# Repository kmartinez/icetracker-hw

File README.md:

# GDP Glacier Monitor

## Name
GDP Glacier Monitor - Hardware - part of the glacsweb.org project at The University of Southampton

## File Info
```
├── GlacTracker_PSU_V1
│   ├── GlacTracker_PSU.brd - EAGLE board file
│   ├── GlacTracker_PSU.sch - EAGLE schematic file
│   ├── GlacTracker_PSU_BOM.xlsx - Overall BOM
│   ├── mgc1g18_GlacTracker_PSU.zip - Gerber Files
│   ├── mgc1g18_GlacTracker_PSU_JLC_bom.xls - BOM for JLC pick and place
│   ├── mgc1g18_GlacTracker_PSU_top_cpl.csv - CPL for JLC pick and place
├── GlacTrackerMCU_V1 
│   ├── GlacTracker.brd - EAGLE board file
│   ├── GlacTracker.sch - EAGLE schematic file
│   ├── mgc1g18_GlacTrackerMCU.zip - Gerber Files
├── GlacTrackerMCU_V2
│   ├── GlacTracker.brd - EAGLE board file
│   ├── GlacTracker.sch - EAGLE schematic file
├── GlacTracker7 - an Eagle7 respin of the separate PSU and MCU boards into a single board
│   ├── tracker.brd - EAGLE board file
│   ├── tracker.sch - EAGLE schematic file
```

### GlacTracker3
This is in IT3 (IceTracker3) and will be the second deployed system in Iceland in 2023.
It has a simplified PSU: 3.3V and 4V with added FET switches to control power to various modules.
The GSM and SWARM are swappable and only one can be installed (to avoid issues with UARTS and we only need one)
It relies on several commercial boards: thing+, sparkfun ublox m9 GPS, sparkfun SWARM, Adafruit SD and Ardusimple's version of Xbee radio.

## GlacTracker_PSU
GlacTracker_PSU designed first to provide 3 configurable supplies through the MP2155 switching regulators. As well as a connection to the "battery" (the output of the BQ24074 Li-Ion battery Charger)
* The default settings are:
    * 3.3V
    * VCC_1 (set to 3.3V) with an optional 3.3V LDO which can be enabled by setting VCC_1 to around 4V (by changing resistor values) and connecting jumpers.
    * 5V
    * V_GSM - connection to the "battery" as described above

Each of these supplies can be enabled or disabled through both on board jumpers and via an external 6-way JST connector meaning when all supplies are disabled the leakage current is very low.

After testing it was found that using the V_GSM connector to power the GSM module was not viable as it cannot operate on voltages below 3.3V. Given this system uses Li-Ion batteries that can go as low as 2.8V, this was not a viable option.

Instead VCC_1 was set to 4V by changing R8 to 120k and two 470uF capacitors were added to the V_BAT input on the GSM module to handle current spikes during transmission. This means GSM can be used in all battery charge states.

* The current supply is setup as follows:
    * 3.3V - used to power MCU, GPS and radio. Enabled via RTC alarm enable circuit
    * VCC_1 - set to 4V used to power GSM. Enabled by MCU on demand
    * 5V - used to power SWARM. Enabled by MCU on demand
    * V_GSM - NO LONGER USED TO POWER GSM, when enabled can be used to read V_BAT

### Changes for V2
* V_GSM is now redundant as is being powered through 4V supply
* LDO is not being used to can be removed

# GlacTrackerMCU
This is the the "MCU" board with the MCU, GPS, Radio, GSM & SWARM.

The hardware is the same for a base station and rover, however the GSM & SWARM modules are not fitted on the rovers.

### GlacTrackerMCU_V2
Contains minor changes from V1 that were discovered after V1 had been "ordered":
* Capacitors added to V_BAT pin of GSM
* Diode removed from PSU_EN as not required.

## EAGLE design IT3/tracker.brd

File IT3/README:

this is the final PCB design used in 2023/4

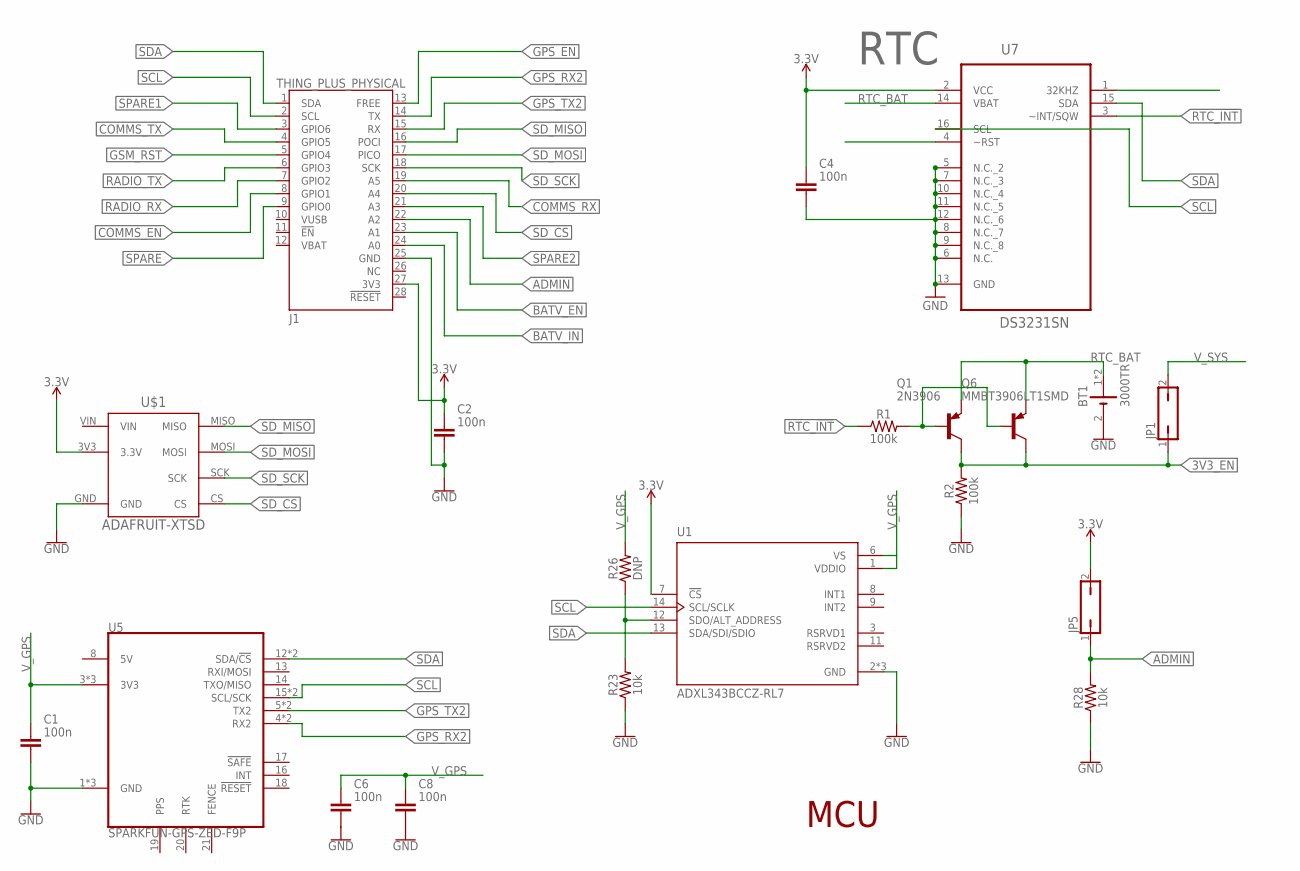
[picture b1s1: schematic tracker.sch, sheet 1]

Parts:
BT1: 3000TR; BAT_3000TR
C1, C2, C4, C6, C8: 100n; CAPC1608X85
J1: THING_PLUS_PHYSICAL; THING_PLUS
JP1, JP5: JP1Q; JP1
Q1: 2N3906; TO92
Q6: MMBT3906LT1SMD; SOT23-BEC
R1, R2: 100k; 0603
R23, R28: 10k; 0603
R26: DNP; 0603
U1: ADXL343BCCZ-RL7; PQFN80P300X500X100-14N
U5: SPARKFUN-GPS-ZED-F9P
U7: DS3231SN; SOIC127P1032X265-16N
U$1: ADAFRUIT-XTSD

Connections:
3.3V: C2.1, C4.1, J1.27 (3V3), JP5.2, U1.7 (!CS), U7.2 (VCC), U$1.3V3 (3.3V); also elsewhere on the board
3V3_EN: JP1.1, Q1.1 (C), Q6.C, R2.2; also elsewhere on the board
ADMIN: J1.22 (A2), JP5.1, R28.2
BATV_EN: J1.23 (A1); also elsewhere on the board
BATV_IN: J1.24 (A0); also elsewhere on the board
COMMS_EN: J1.8 (GPIO1); also elsewhere on the board
COMMS_RX: J1.19 (A5); also elsewhere on the board
COMMS_TX: J1.4 (GPIO5); also elsewhere on the board
GND: BT1.2 (-), C1.2, C2.2, C4.2, C6.2, C8.2, J1.25 (GND), R2.1, R23.1, R28.1, U1.2 (GND), U1.4 (GND), U1.5 (GND), U5.1 (GND), U5.7 (GND), U5.25 (GND), U7.5 (N.C._2), U7.6 (N.C.), U7.7 (N.C._3), U7.8 (N.C._7), U7.9 (N.C._8), U7.10 (N.C._4), U7.11 (N.C._5), U7.12 (N.C._6), U7.13 (GND), U$1.GND; also elsewhere on the board
GPS_EN: J1.13 (FREE); also elsewhere on the board
GPS_RX2: J1.14 (TX), U5.4 (RX2), U5.11 (RX2)
GPS_TX2: J1.15 (RX), U5.5 (TX2), U5.10 (TX2)
GSM_RST: J1.5 (GPIO4); also elsewhere on the board
unnamed: R23.2, R26.1, U1.12 (SDO/ALT_ADDRESS)
unnamed: Q1.2 (B), Q6.B, R1.2
RADIO_RX: J1.7 (GPIO2); also elsewhere on the board
RADIO_TX: J1.6 (GPIO3); also elsewhere on the board
RTC_!INT: R1.1, U7.3 (~INT/SQW)
RTC_BAT: BT1.1 (+), BT1.3 (+), Q1.3 (E), Q6.E, U7.14 (VBAT)
SCL: J1.2 (SCL), U1.14 (SCL/SCLK), U5.15 (SCL/SCK), U5.22 (SCL/SCK), U7.16 (SCL)
SDA: J1.1 (SDA), U1.13 (SDA/SDI/SDIO), U5.12 (SDA/!CS), U5.23 (SDA/!CS), U7.15 (SDA)
SD_CS: J1.20 (A4), U$1.CS
SD_MISO: J1.16 (POCI), U$1.MISO
SD_MOSI: J1.17 (PICO), U$1.MOSI
SD_SCK: J1.18 (SCK), U$1.SCK
SPARE: J1.9 (GPIO0)
SPARE1: J1.3 (GPIO6)
SPARE2: J1.21 (A3)
V_GPS: C1.1, C6.1, C8.1, R26.2, U1.1 (VDDIO), U1.6 (VS), U5.3 (3V3), U5.9 (3V3), U5.24 (3V3); also elsewhere on the board
V_SYS: JP1.2; also elsewhere on the board

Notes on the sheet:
MCU
RTC

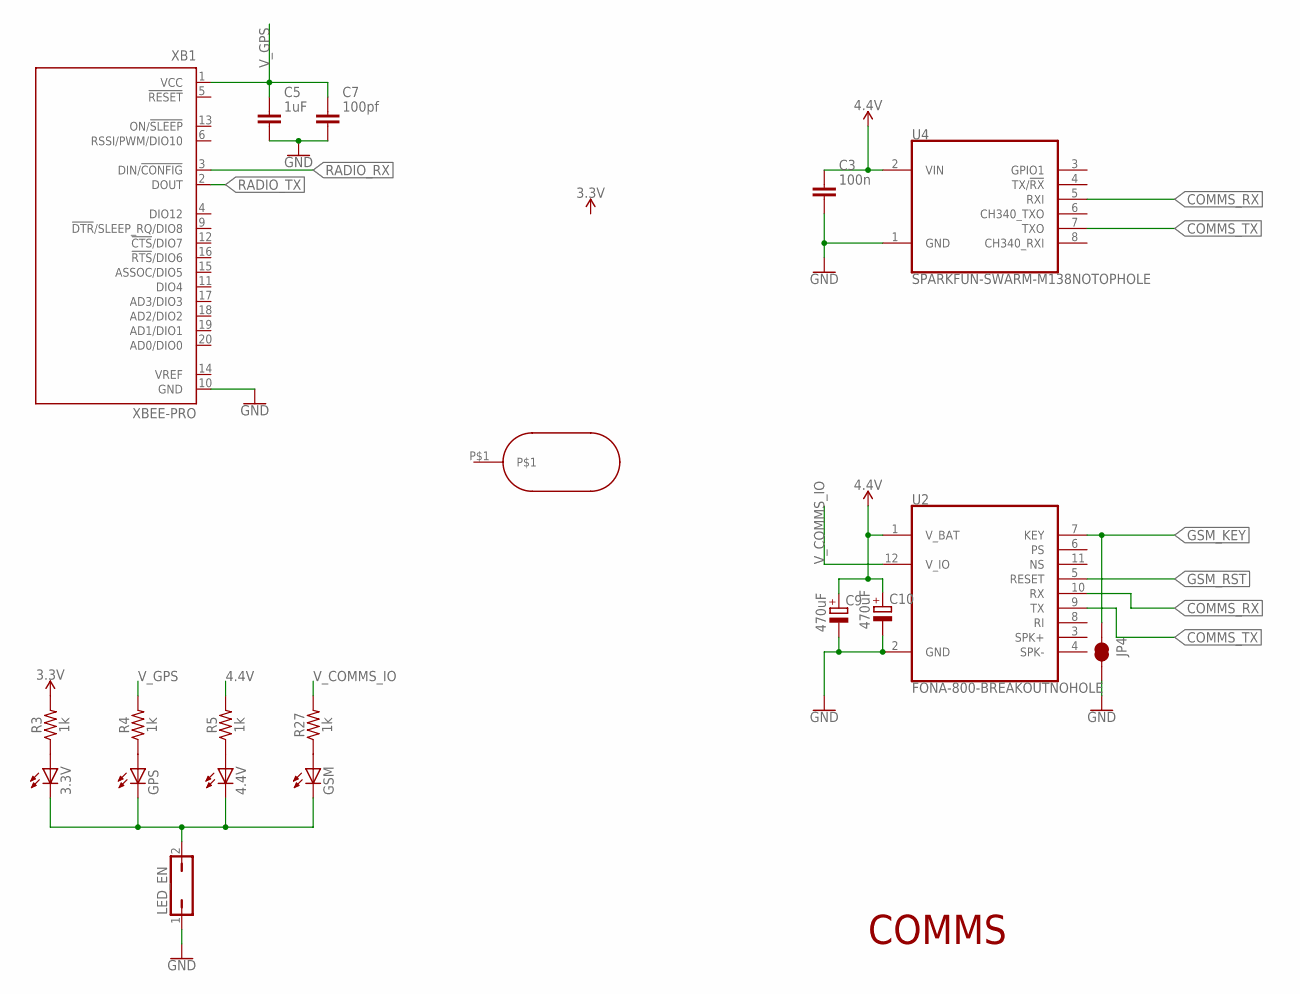
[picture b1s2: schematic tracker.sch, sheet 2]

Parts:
3.3V, 4.4V: LEDCHIP-LED0805; CHIP-LED0805
C3: 100n; CAPC1608X85
C5: 1uF; CAPC1608X85
C7: 100pf; CAPC1608X85
C9, C10: 470uF; CAPPRD508W65D1000H1100B
GPS: LEDCHIP-LED0805; CHIP-LED0805
GSM: LEDCHIP-LED0805; CHIP-LED0805
JP4: JUMPER-SMT_2_NC_TRACE_SILK; SMT-JUMPER_2_NC_TRACE_SILK
LED_EN: JP1Q; JP1
R3, R4, R5, R27: 1k; 0603
U2: FONA-800-BREAKOUTNOHOLE; FONA-800-BREAKOUT-NH
U4: SPARKFUN-SWARM-M138NOTOPHOLE; SPARKFUN-SWARM-M138-NTH
U$2: SLOT130.5
XB1: XBEE-PRO

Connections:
3.3V: R3.2; also elsewhere on the board
4.4V: C3.1, C9.1 (+), C10.1 (+), R5.2, U2.1 (V_BAT), U4.2 (VIN); also elsewhere on the board
COMMS_RX: U2.10 (RX), U4.5 (RXI); also elsewhere on the board
COMMS_TX: U2.9 (TX), U4.7 (TXO); also elsewhere on the board
GND: C3.2, C5.2, C7.2, C9.2 (-), C10.2 (-), JP4.2, LED_EN.1, U2.2 (GND), U4.1 (GND), XB1.10 (GND); also elsewhere on the board
GSM_KEY: JP4.1, U2.7 (KEY)
GSM_RST: U2.5 (RESET); also elsewhere on the board
unnamed: 3.3V.C, 4.4V.C, GPS.C, GSM.C, LED_EN.2
unnamed: GPS.A, R4.1
unnamed: 3.3V.A, R3.1
unnamed: GSM.A, R27.1
unnamed: 4.4V.A, R5.1
RADIO_RX: XB1.3 (DIN/!CONFIG); also elsewhere on the board
RADIO_TX: XB1.2 (DOUT); also elsewhere on the board
V_COMMS_IO: R27.2, U2.12 (V_IO); also elsewhere on the board
V_GPS: C5.1, C7.1, R4.2, XB1.1 (VCC); also elsewhere on the board

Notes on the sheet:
COMMS

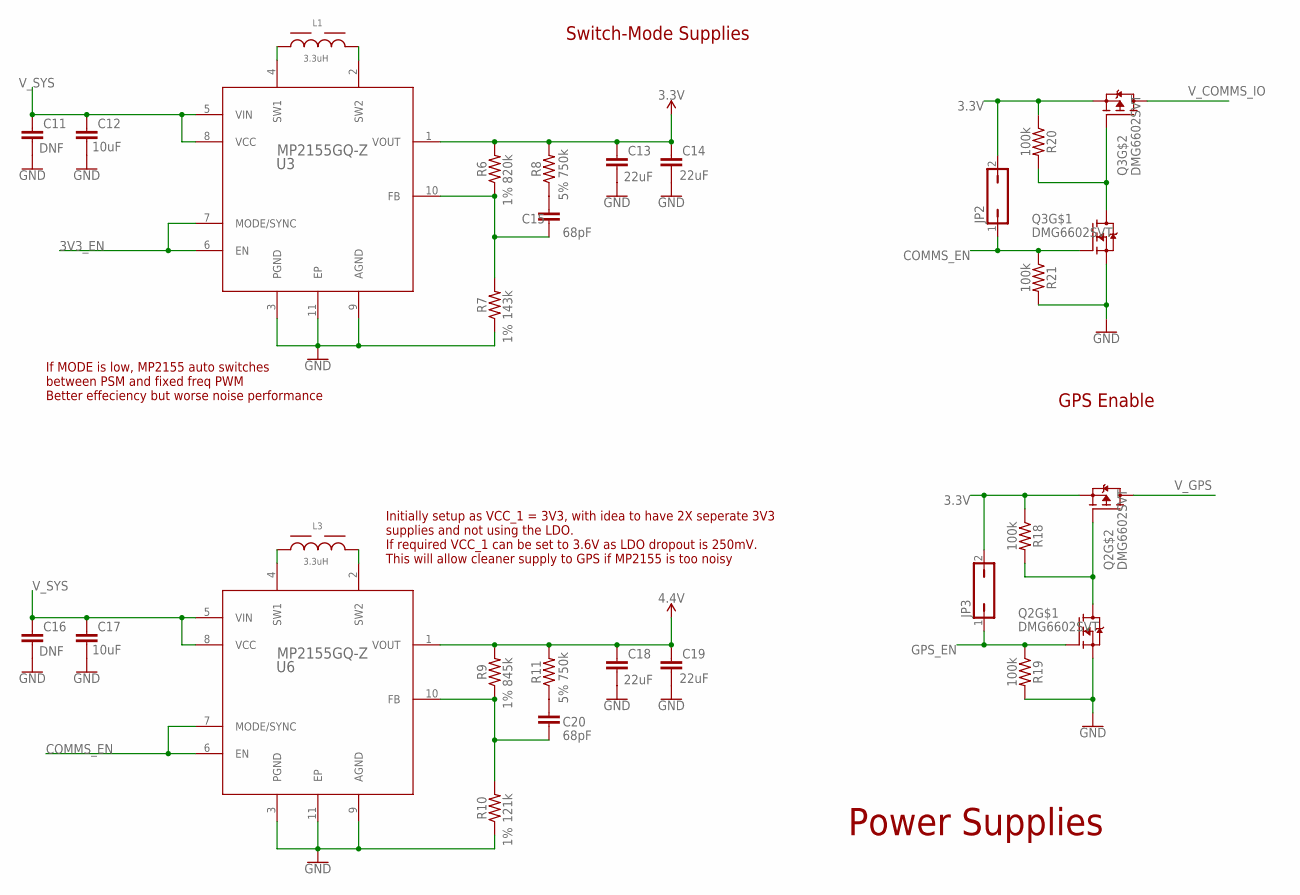
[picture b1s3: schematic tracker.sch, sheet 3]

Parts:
C11, C16: DNF; CAPC2012X110
C12, C17: 10uF; CAPC2012X110; VOLTAGE_RATING 6.3V
C13, C14, C18, C19: 22uF; CAPC2012X110; VOLTAGE_RATING 10V
C15, C20: 68pF; CAPC1608X85; VOLTAGE_RATING 50V
JP2, JP3: JP1Q; JP1
L1, L3: 3.3uH; WE-HCI_7050
Q2, Q3: DMG6602SVT; TSOT26
R6: 820k; 0603; TOLERANCE 1%
R7: 143k; 0603; TOLERANCE 1%
R8, R11: 750k; 0603; TOLERANCE 5%
R9: 845k; 0603; TOLERANCE 1%
R10: 121k; 0603; TOLERANCE 1%
R18, R19, R20, R21: 100k; 0603
U3, U6: MP2155GQ-Z; QFN-10_MP2155_MNP

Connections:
3.3V: C13.1, C14.1, JP2.2, JP3.2, Q2.P$2 (S), Q3.P$2 (S), R6.2, R8.2, R18.1, R20.1, U3.1 (VOUT); also elsewhere on the board
3V3_EN: U3.6 (EN), U3.7 (MODE/SYNC); also elsewhere on the board
4.4V: C18.1, C19.1, R9.2, R11.2, U6.1 (VOUT); also elsewhere on the board
COMMS_EN: JP2.1, Q3.P$1 (G), R21.1, U6.6 (EN), U6.7 (MODE/SYNC); also elsewhere on the board
GND: C11.2, C12.2, C13.2, C14.2, C16.2, C17.2, C18.2, C19.2, Q2.P$5 (S), Q3.P$5 (S), R7.1, R10.1, R19.2, R21.2, U3.3 (PGND), U3.9 (AGND), U3.11 (EP), U6.3 (PGND), U6.9 (AGND), U6.11 (EP); also elsewhere on the board
GPS_EN: JP3.1, Q2.P$1 (G), R19.1; also elsewhere on the board
unnamed: C15.2, R6.1, R7.2, U3.10 (FB)
unnamed: C15.1, R8.1
unnamed: L1.1, U3.4 (SW1)
unnamed: L1.2, U3.2 (SW2)
unnamed: C20.2, R9.1, R10.2, U6.10 (FB)
unnamed: C20.1, R11.1
unnamed: L3.1, U6.4 (SW1)
unnamed: L3.2, U6.2 (SW2)
unnamed: Q2.P$3 (G), Q2.P$6 (D), R18.2
unnamed: Q3.P$3 (G), Q3.P$6 (D), R20.2
V_COMMS_IO: Q3.P$4 (D); also elsewhere on the board
V_GPS: Q2.P$4 (D); also elsewhere on the board
V_SYS: C11.1, C12.1, C16.1, C17.1, U3.5 (VIN), U3.8 (VCC), U6.5 (VIN), U6.8 (VCC); also elsewhere on the board

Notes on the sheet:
Initially setup as VCC_1 = 3V3, with idea to have 2X seperate 3V3 supplies and not using the LDO. If required VCC_1 can be set to 3.6V as LDO dropout is 250mV. This will allow cleaner supply to GPS if MP2155 is too noisy
Power Supplies
If MODE is low, MP2155 auto switches between PSM and fixed freq PWM Better effeciency but worse noise performance
Switch-Mode Supplies
GPS Enable

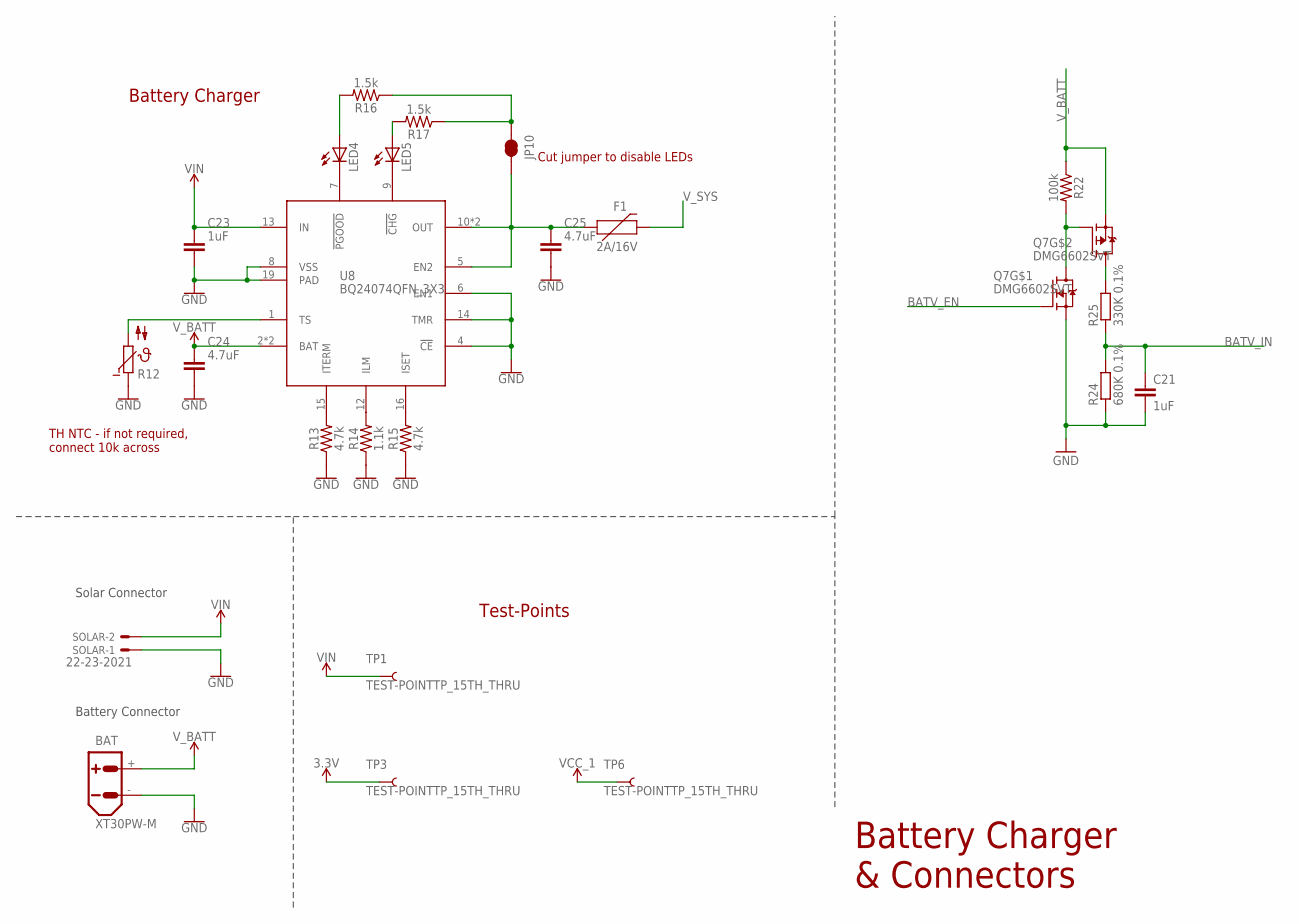
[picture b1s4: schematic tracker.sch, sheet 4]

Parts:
BAT: XT30PW-M
C21: 1uF; C0805
C23: 1uF; CAPC2012X110
C24, C25: 4.7uF; CAPC2012X110
F1: 2A/16V; F1812
JP10: JUMPER-SMT_2_NC_TRACE_SILK; SMT-JUMPER_2_NC_TRACE_SILK
LED4, LED5: LEDSML0805; SML0805
Q7: DMG6602SVT; TSOT26
R12: DNF; P640
R13, R15: 4.7k; 0603
R14: 1.1k; 0603
R16, R17: 1.5k; 0603
R22: 100k; 0603
R24: 680K 0.1%; R0805
R25: 330K 0.1%; R0805
SOLAR: 22-23-2021
TP1, TP3, TP6: TEST-POINTTP_15TH_THRU; TP_15TH
U8: BQ24074QFN_3X3; QFN_3X3

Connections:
3.3V: TP3.P$1; also elsewhere on the board
4.4V: TP6.P$1; also elsewhere on the board
BATV_EN: Q7.P$1 (G); also elsewhere on the board
BATV_IN: C21.1, R24.2, R25.1; also elsewhere on the board
GND: BAT.-, C21.2, C23.2, C24.2, C25.2, Q7.P$5 (S), R12.1, R13.1, R14.1, R15.1, R24.1, SOLAR.1, U8.4 (!CE), U8.6 (EN1), U8.8 (VSS), U8.14 (TMR), U8.19 (PAD); also elsewhere on the board
unnamed: Q7.P$3 (G), Q7.P$6 (D), R22.2
unnamed: R12.2, U8.1 (TS)
unnamed: R13.2, U8.15 (ITERM)
unnamed: R14.2, U8.12 (ILM)
unnamed: R15.2, U8.16 (ISET)
unnamed: LED4.C, U8.7 (!PGOOD)
unnamed: LED5.C, U8.9 (!CHG)
unnamed: JP10.1, R16.1, R17.1
unnamed: LED4.A, R16.2
unnamed: LED5.A, R17.2
unnamed: C25.1, F1.1, JP10.2, U8.5 (EN2), U8.10 (OUT), U8.11 (OUT)
VCC_HP2_SW1: Q7.P$4 (D), R25.2
VIN: C23.1, SOLAR.2, TP1.P$1, U8.13 (IN)
V_BATT: BAT.+, C24.1, Q7.P$2 (S), R22.1, U8.2 (BAT), U8.3 (BAT)
V_SYS: F1.2; also elsewhere on the board

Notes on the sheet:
TH NTC - if not required, connect 10k across
Battery Charger & Connectors
Cut jumper to disable LEDs
Battery Charger
Test-Points
Battery Connector
Solar Connector

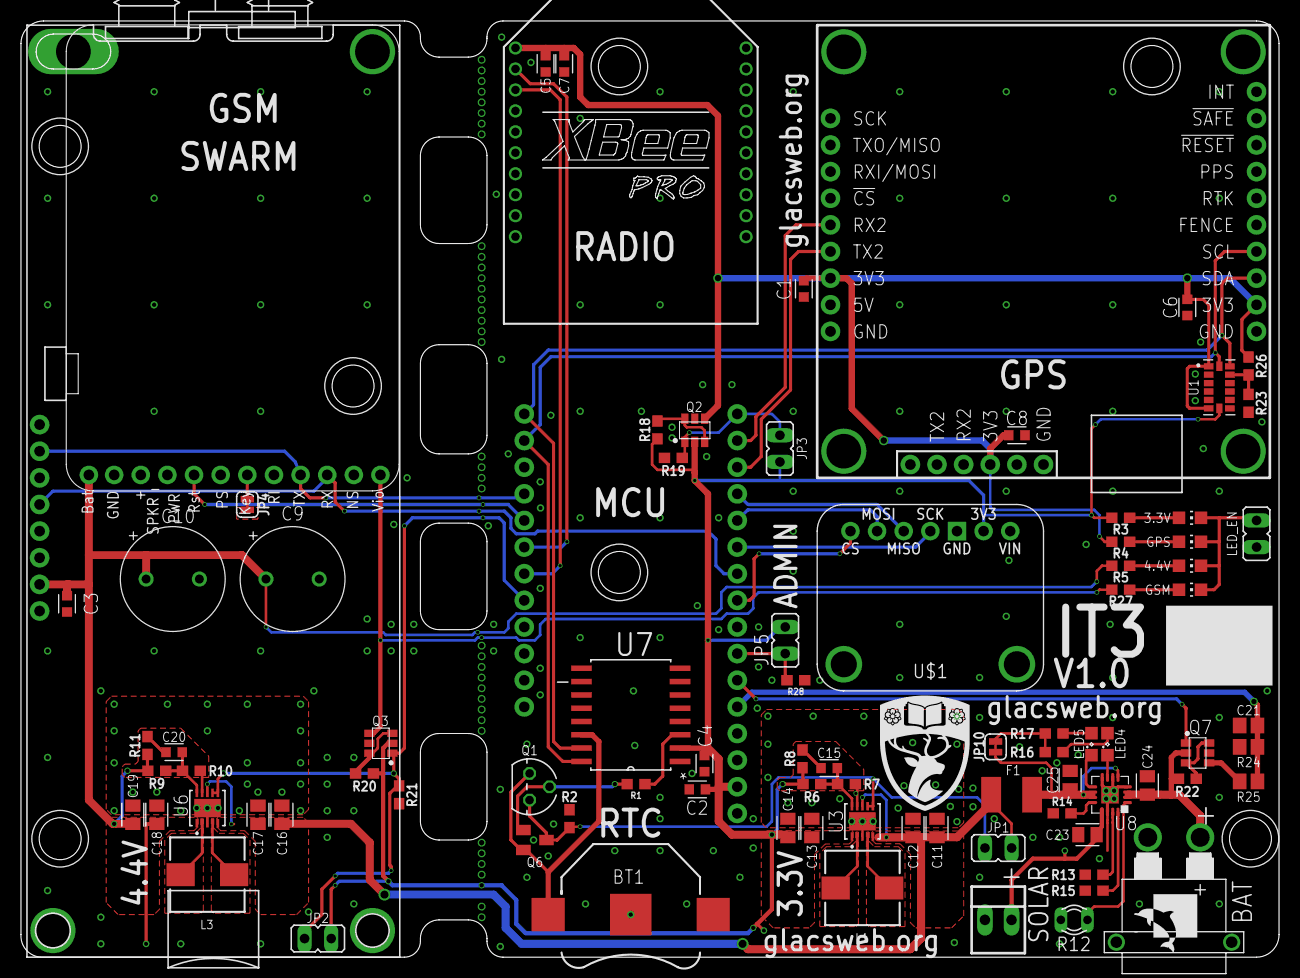
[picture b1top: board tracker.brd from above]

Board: 2 copper layers, 120.0 x 89.3 mm, 91 parts (0 on the bottom side), 59 nets.

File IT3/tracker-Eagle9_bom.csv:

Comment,Designator,Footprint,LCSC Part #
,3.3V,CHIP-LED0805,C142303
,4.4V,CHIP-LED0805,C142303
,GPS,CHIP-LED0805,C142303
,GSM,CHIP-LED0805,C142303
,JP1,JP1,
,JP2,JP1,
,JP3,JP1,
,JP5,JP1,
,LED_EN,JP1,
,LED4,SML0805,C142303
,LED5,SML0805,C142303
 820k,R6,0603,
 845k,R9,0603,
1.1k,R14,0603,
1.5k,R16 R17,0603,
1k,R3 R4 R5 R27,0603,
1uF,C21,C0805,
1uF,C5,CAPC1608X85,C105524
1uF,C23,CAPC2012X110,C318694
2A/16V,F1,F1812,C70126
2N3906,Q1,TO92,
3.3uH,L1 L3,WE-HCI_7050,
4.7k,R13 R15,0603,
4.7uF,C24 C25,CAPC2012X110,C730468
10k,R23 R28,0603,
10uF,C12 C17,CAPC2012X110,C162430
22-23-2021,SOLAR,22-23-2021,
22uF,C13 C14 C18 C19,CAPC2012X110,C77074
68pF,C15 C20,CAPC1608X85,C779986
100k,R1 R2 R18 R19 R20 R21 R22,0603,
100n,C1 C2 C3 C4 C6 C8,CAPC1608X85,C913910
100pf,C7,CAPC1608X85,C307357
143k,R7,0603,
121k,R10,0603,
340K 0.1%,R25,R0805,C865414
470uF,C9 C10,CAPPRD508W65D1000H1100B,
680K 0.1%,R24,R0805,C445667
750k,R8 R11,0603,
3000TR,BT1,BAT_3000TR,C964830
ADAFRUIT-XTSD,U$1,ADAFRUIT-XTSD,
ADXL343BCCZ-RL7,U1,PQFN80P300X500X100-14N,
BQ24074QFN_3X3,U8,QFN_3X3,C54313
DMG6602SVT,Q2 Q3 Q7,TSOT26,C110497
DNF,C11 C16,CAPC2012X110,
DNF,R12,P640,
DNP,R26,0603,
DS3231SN,U7,SOIC127P1032X265-16N,
FONA-800-BREAKOUTNOHOLE,U2,FONA-800-BREAKOUT-NH,
JUMPER-SMT_2_NC_TRACE_SILK,JP4 JP10,SMT-JUMPER_2_NC_TRACE_SILK,
MMBT3906LT1SMD,Q6,SOT23-BEC,C53444
MP2155GQ-Z,U3 U6,QFN-10_MP2155_MNP,
SLOT130.5,U$2,SLOT130.5,
SPARKFUN-GPS-ZED-F9P,U5,SPARKFUN-GPS-ZED-F9P,
SPARKFUN-SWARM-M138NOTOPHOLE,U4,SPARKFUN-SWARM-M138-NTH,
TEST-POINTTP_15TH_THRU,TP1 TP3 TP6,TP_15TH,
THING_PLUS_PHYSICAL,J1,THING_PLUS,
XBEE-PRO,XB1,XBEE-PRO,
XT30PW-M,BAT,XT30PW-M,

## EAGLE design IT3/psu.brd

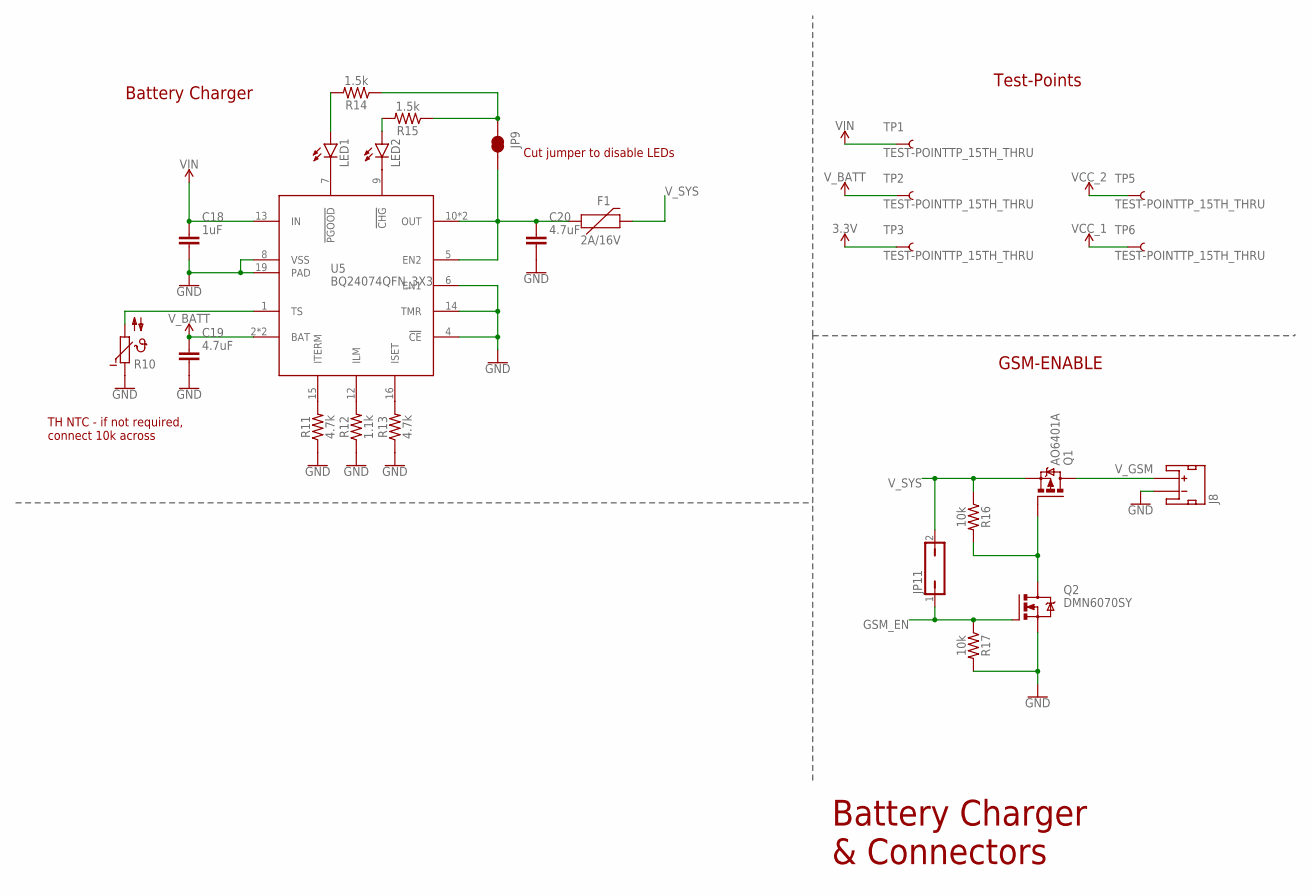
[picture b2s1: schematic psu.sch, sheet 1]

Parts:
C18: 1uF; CAPC2012X110
C19, C20: 4.7uF; CAPC2012X110
F1: 2A/16V; F1812
J8: JST_2MM_MALE; JST-2-SMD
JP9: JUMPER-SMT_2_NC_TRACE_SILK; SMT-JUMPER_2_NC_TRACE_SILK
JP11: JP1Q; JP1
LED1, LED2: LEDSML0805; SML0805
Q1: AO6401A; TSOP-6
Q2: DMN6070SY; SOT-89-3
R10: DNF; P640
R11, R13: 4.7k; 0603
R12: 1.1k; 0603
R14, R15: 1.5k; 0603
R16, R17: 10k; 0603
TP1, TP2, TP3, TP5, TP6: TEST-POINTTP_15TH_THRU; TP_15TH
U5: BQ24074QFN_3X3; QFN_3X3

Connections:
3.3V: TP3.P$1; also elsewhere on the board
GND: C18.2, C19.2, C20.2, J8.1 (-), Q2.3 (S), R10.1, R11.1, R12.1, R13.1, R17.2, U5.4 (!CE), U5.6 (EN1), U5.8 (VSS), U5.14 (TMR), U5.19 (PAD); also elsewhere on the board
GSM_EN: JP11.1, Q2.1 (G), R17.1
unnamed: R10.2, U5.1 (TS)
unnamed: R11.2, U5.15 (ITERM)
unnamed: R12.2, U5.12 (ILM)
unnamed: R13.2, U5.16 (ISET)
unnamed: LED1.C, U5.7 (!PGOOD)
unnamed: LED2.C, U5.9 (!CHG)
unnamed: JP9.1, R14.1, R15.1
unnamed: LED1.A, R14.2
unnamed: LED2.A, R15.2
unnamed: C20.1, F1.1, JP9.2, U5.5 (EN2), U5.10 (OUT), U5.11 (OUT)
unnamed: Q1.3 (G), Q2.2 (D), Q2.4 (D), R16.2
VCC_1: TP6.P$1; also elsewhere on the board
VCC_2: TP5.P$1; also elsewhere on the board
VIN: C18.1, TP1.P$1, U5.13 (IN)
V_BATT: C19.1, TP2.P$1, U5.2 (BAT), U5.3 (BAT)
V_GSM: J8.2 (+), Q1.1 (D), Q1.2 (D), Q1.5 (D), Q1.6 (D)
V_SYS: F1.2, JP11.2, Q1.4 (S), R16.1; also elsewhere on the board

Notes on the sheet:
TH NTC - if not required, connect 10k across
Battery Charger & Connectors
Cut jumper to disable LEDs
Battery Charger
Test-Points
GSM-ENABLE

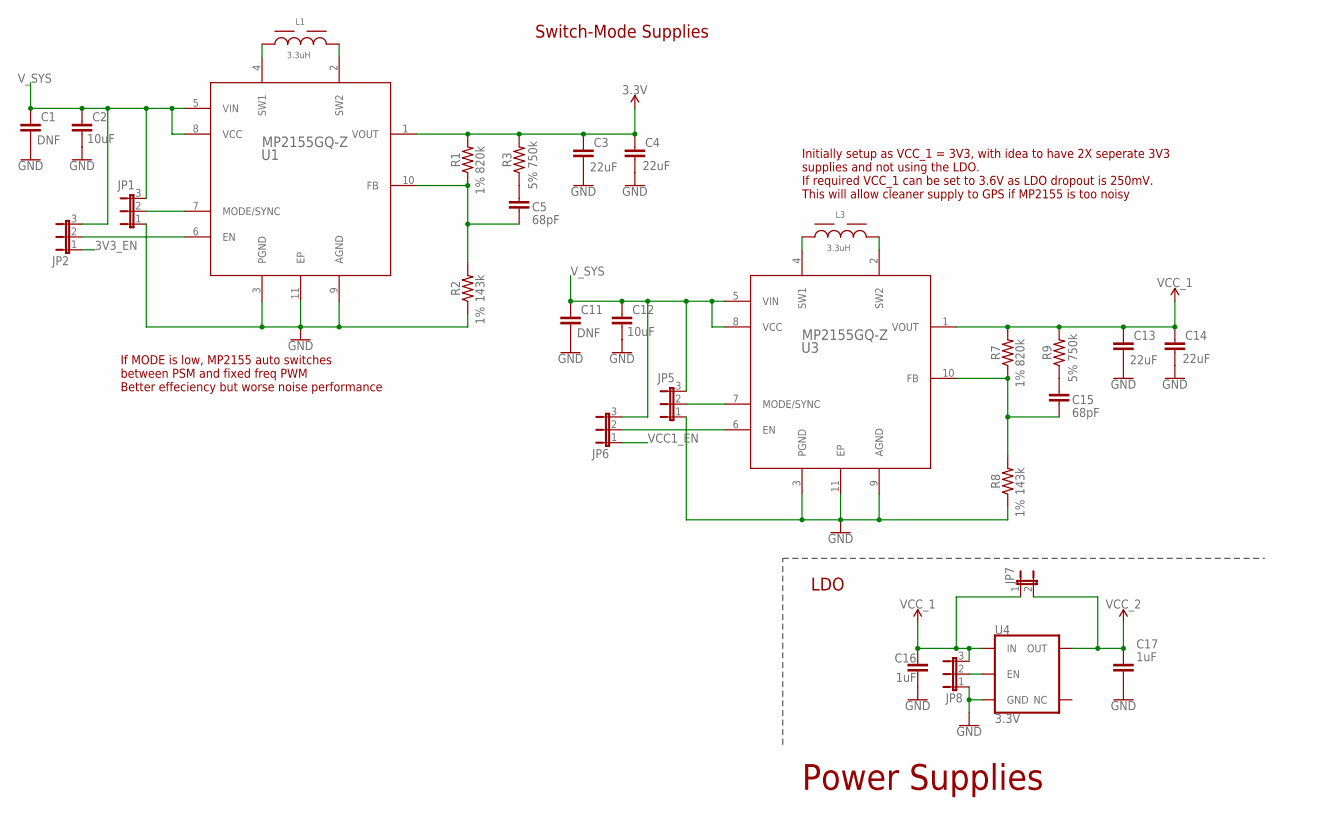
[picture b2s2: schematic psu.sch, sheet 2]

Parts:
C1, C11: DNF; CAPC2012X110
C2, C12: 10uF; CAPC2012X110; VOLTAGE_RATING 6.3V
C3, C4, C13, C14: 22uF; CAPC2012X110; VOLTAGE_RATING 10V
C5, C15: 68pF; CAPC1608X85; VOLTAGE_RATING 50V
C16, C17: 1uF; CAPC2012X110
JP1, JP2, JP5, JP6, JP8: JP2E; JP2
JP7: JP1E; JP1
L1, L3: 3.3uH; WE-HCI_7050
R1, R7: 820k; 0603; TOLERANCE 1%
R2, R8: 143k; 0603; TOLERANCE 1%
R3, R9: 750k; 0603; TOLERANCE 5%
U1, U3: MP2155GQ-Z; QFN-10_MP2155_MNP
U4: 3.3V; SOT23-5

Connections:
3.3V: C3.1, C4.1, R1.2, R3.2, U1.1 (VOUT); also elsewhere on the board
3V3_EN: JP2.1
GND: C1.2, C2.2, C3.2, C4.2, C11.2, C12.2, C13.2, C14.2, C16.2, C17.2, JP1.1, JP5.1, JP8.1, R2.1, R8.1, U1.3 (PGND), U1.9 (AGND), U1.11 (EP), U3.3 (PGND), U3.9 (AGND), U3.11 (EP), U4.2 (GND); also elsewhere on the board
unnamed: C5.1, R3.1
unnamed: JP1.2, U1.7 (MODE/SYNC)
unnamed: C5.2, R1.1, R2.2, U1.10 (FB)
unnamed: JP2.2, U1.6 (EN)
unnamed: L1.1, U1.4 (SW1)
unnamed: L1.2, U1.2 (SW2)
unnamed: JP5.2, U3.7 (MODE/SYNC)
unnamed: JP6.2, U3.6 (EN)
unnamed: C15.2, R7.1, R8.2, U3.10 (FB)
unnamed: C15.1, R9.1
unnamed: L3.1, U3.4 (SW1)
unnamed: L3.2, U3.2 (SW2)
unnamed: JP8.2, U4.3 (EN)
VCC1_EN: JP6.1
VCC_1: C13.1, C14.1, C16.1, JP7.1, JP8.3, R7.2, R9.2, U3.1 (VOUT), U4.1 (IN); also elsewhere on the board
VCC_2: C17.1, JP7.2, U4.5 (OUT); also elsewhere on the board
V_SYS: C1.1, C2.1, C11.1, C12.1, JP1.3, JP2.3, JP5.3, JP6.3, U1.5 (VIN), U1.8 (VCC), U3.5 (VIN), U3.8 (VCC); also elsewhere on the board

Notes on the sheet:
Initially setup as VCC_1 = 3V3, with idea to have 2X seperate 3V3 supplies and not using the LDO. If required VCC_1 can be set to 3.6V as LDO dropout is 250mV. This will allow cleaner supply to GPS if MP2155 is too noisy
Power Supplies
If MODE is low, MP2155 auto switches between PSM and fixed freq PWM Better effeciency but worse noise performance
LDO
Switch-Mode Supplies

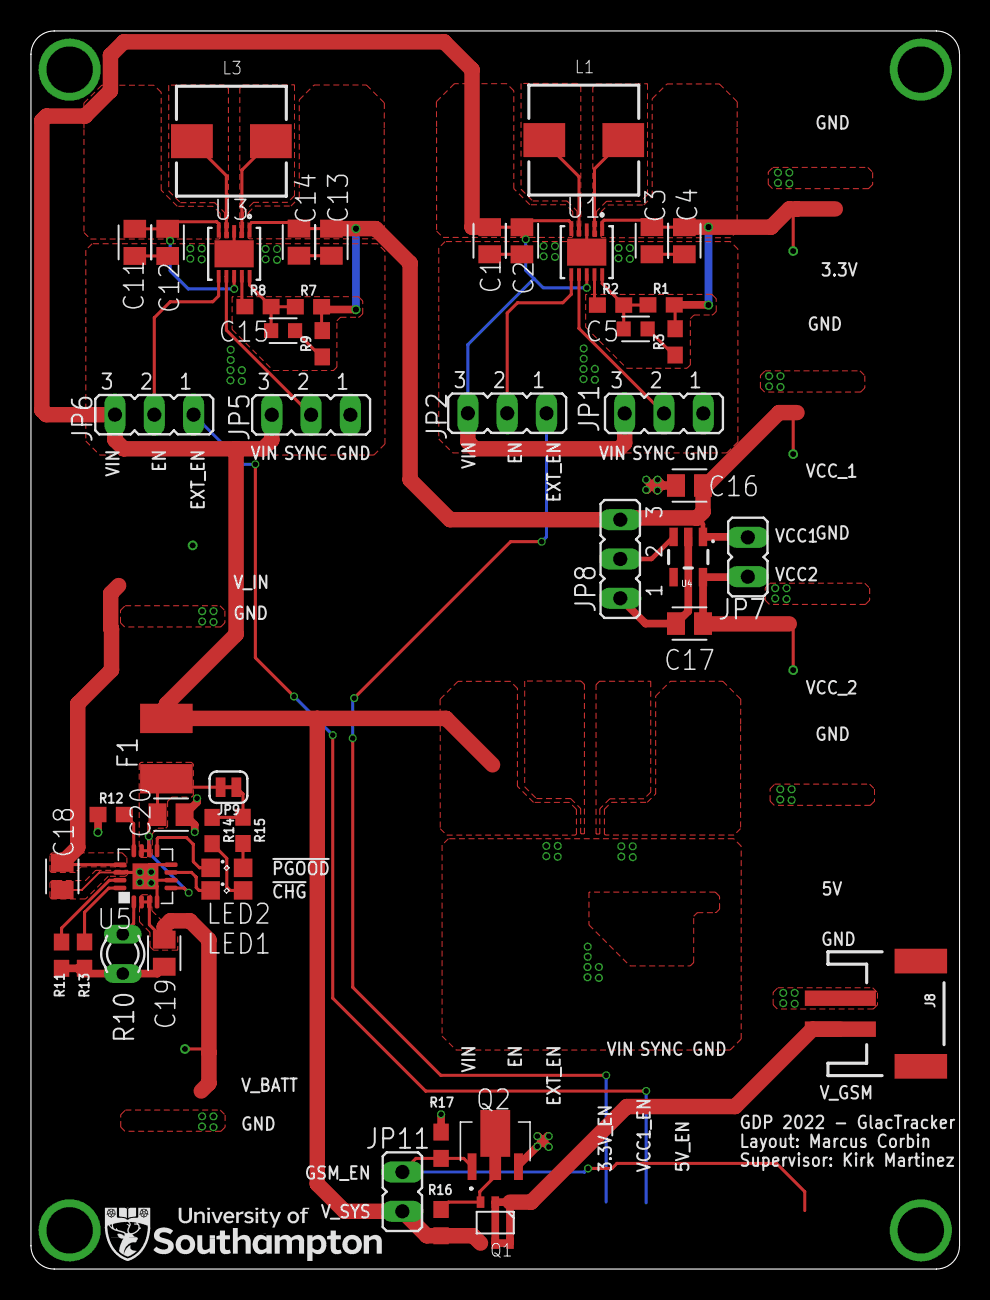
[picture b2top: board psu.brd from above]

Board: 2 copper layers, 60.0 x 80.0 mm, 54 parts (0 on the bottom side), 33 nets.

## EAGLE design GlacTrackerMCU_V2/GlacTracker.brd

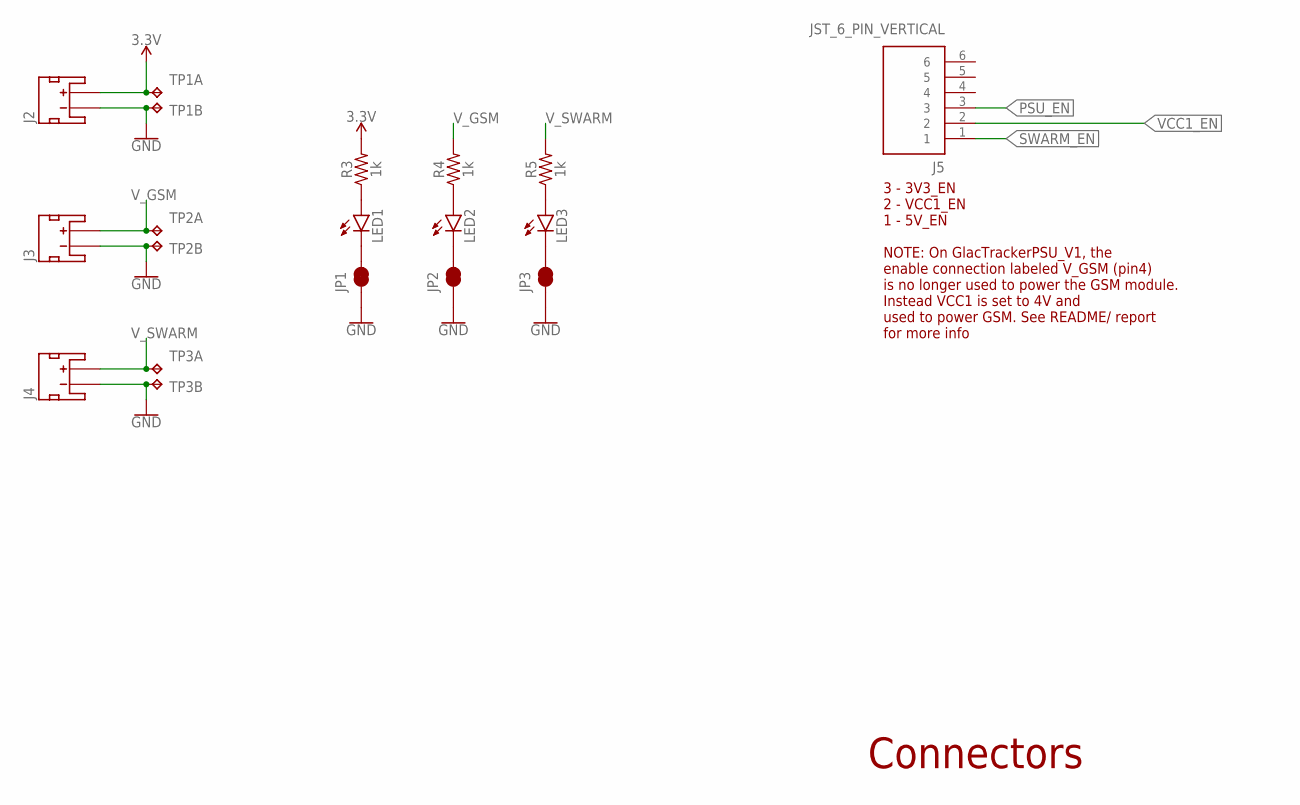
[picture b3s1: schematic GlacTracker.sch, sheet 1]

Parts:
J2, J3, J4: JST_2MM_MALE; JST-2-SMD
J5: JST_6_PIN_VERTICAL; JST-6-SMD-VERT-1.0MM
JP1, JP2, JP3: JUMPER-SMT_2_NC_TRACE_SILK; SMT-JUMPER_2_NC_TRACE_SILK
LED1, LED2, LED3: LEDCHIP-LED0805; CHIP-LED0805
R3, R4, R5: 1k; 0603
TP1, TP2, TP3: TP2P2-38-17; P2-38-17

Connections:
3.3V: J2.2 (+), R3.2, TP1.TP-1; also elsewhere on the board
GND: J2.1 (-), J3.1 (-), J4.1 (-), JP1.1, JP2.1, JP3.1, TP1.TP-2, TP2.TP-2, TP3.TP-2; also elsewhere on the board
unnamed: JP1.2, LED1.C
unnamed: JP2.2, LED2.C
unnamed: JP3.2, LED3.C
unnamed: LED1.A, R3.1
unnamed: LED2.A, R4.1
unnamed: LED3.A, R5.1
PSU_EN: J5.3; also elsewhere on the board
SWARM_EN: J5.1; also elsewhere on the board
VCC1_EN: J5.2; also elsewhere on the board
V_GSM: J3.2 (+), R4.2, TP2.TP-1; also elsewhere on the board
V_SWARM: J4.2 (+), R5.2, TP3.TP-1; also elsewhere on the board

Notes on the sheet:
Connectors
3 - 3V3_EN 2 - VCC1_EN 1 - 5V_EN NOTE: On GlacTrackerPSU_V1, the enable connection labeled V_GSM (pin4) is no longer used to power the GSM module. Instead VCC1 is set to 4V and used to power GSM. See README/ report for more info

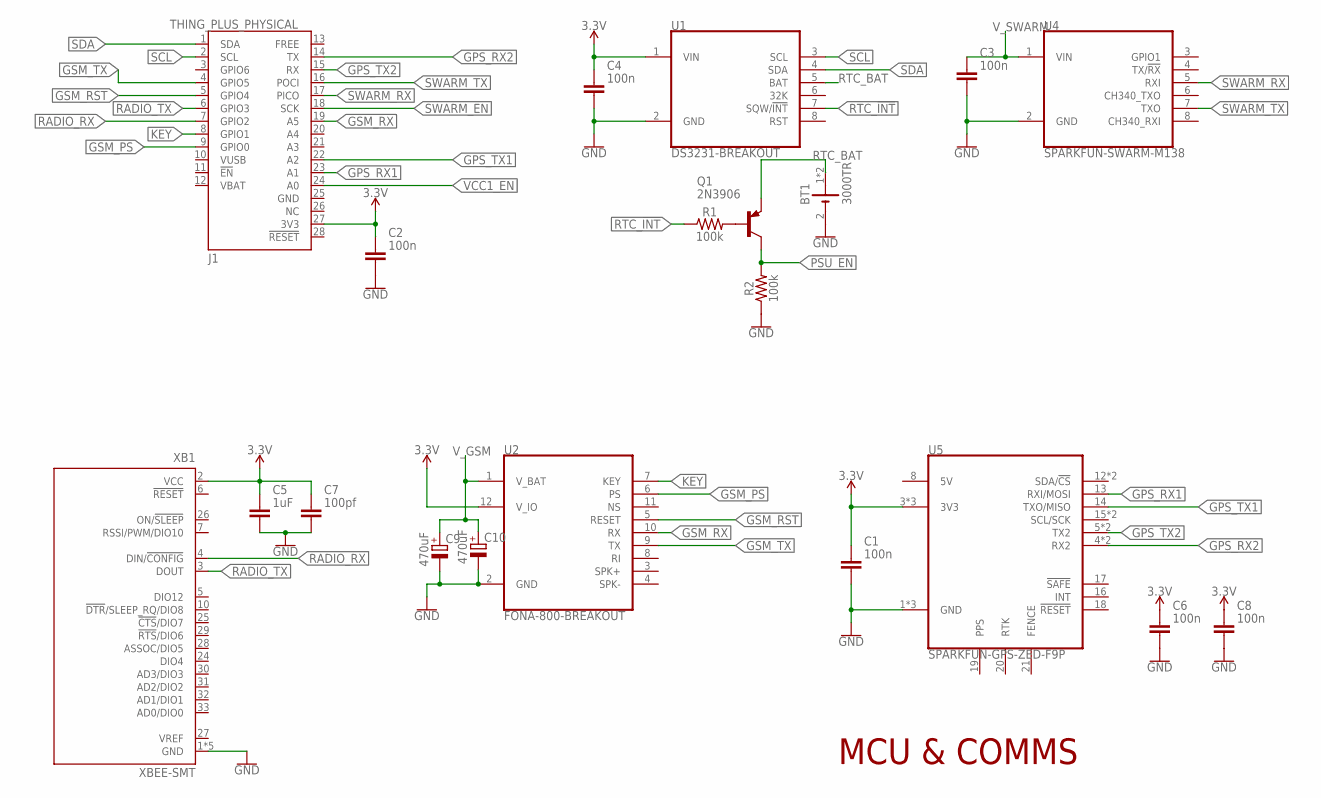
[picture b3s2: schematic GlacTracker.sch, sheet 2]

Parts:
BT1: 3000TR; BAT_3000TR
C1, C2, C3, C4, C6, C8: 100n; CAPC1608X85
C5: 1uF; CAPC1608X85
C7: 100pf; CAPC1608X85
C9, C10: 470uF; CAPPRD508W65D1000H1100B
J1: THING_PLUS_PHYSICAL; THING_PLUS
Q1: 2N3906; TO92
R1, R2: 100k; 0603
U1: DS3231-BREAKOUT
U2: FONA-800-BREAKOUT
U4: SPARKFUN-SWARM-M138
U5: SPARKFUN-GPS-ZED-F9P
XB1: XBEE-SMT

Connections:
3.3V: C1.1, C2.1, C4.1, C5.1, C6.1, C7.1, C8.1, J1.27 (3V3), U1.1 (VIN), U2.12 (V_IO), U5.3 (3V3), U5.9 (3V3), U5.24 (3V3), XB1.2 (VCC); also elsewhere on the board
GND: BT1.2 (-), C1.2, C2.2, C3.2, C4.2, C5.2, C6.2, C7.2, C8.2, C9.2 (-), C10.2 (-), R2.1, U1.2 (GND), U2.2 (GND), U4.2 (GND), U5.1 (GND), U5.7 (GND), U5.25 (GND), XB1.1 (GND), XB1.11 (GND), XB1.13 (GND), XB1.22 (GND), XB1.35 (GND); also elsewhere on the board
GPS_RX1: J1.23 (A1), U5.13 (RXI/MOSI)
GPS_RX2: J1.14 (TX), U5.4 (RX2), U5.11 (RX2)
GPS_TX1: J1.22 (A2), U5.14 (TXO/MISO)
GPS_TX2: J1.15 (RX), U5.5 (TX2), U5.10 (TX2)
GSM_PS: J1.9 (GPIO0), U2.6 (PS)
GSM_RST: J1.5 (GPIO4), U2.5 (RESET)
GSM_RX: J1.19 (A5), U2.10 (RX)
GSM_TX: J1.4 (GPIO5), U2.9 (TX)
KEY: J1.8 (GPIO1), U2.7 (KEY)
unnamed: Q1.2 (B), R1.2
PSU_EN: Q1.1 (C), R2.2; also elsewhere on the board
RADIO_RX: J1.7 (GPIO2), XB1.4 (DIN/!CONFIG)
RADIO_TX: J1.6 (GPIO3), XB1.3 (DOUT)
RTC_!INT: R1.1, U1.7 (SQW/!INT)
RTC_BAT: BT1.1 (+), BT1.3 (+), Q1.3 (E), U1.5 (BAT)
SCL: J1.2 (SCL), U1.3 (SCL)
SDA: J1.1 (SDA), U1.4 (SDA)
SWARM_EN: J1.18 (SCK); also elsewhere on the board
SWARM_RX: J1.17 (PICO), U4.5 (RXI)
SWARM_TX: J1.16 (POCI), U4.7 (TXO)
VCC1_EN: J1.24 (A0); also elsewhere on the board
V_GSM: C9.1 (+), C10.1 (+), U2.1 (V_BAT); also elsewhere on the board
V_SWARM: C3.1, U4.1 (VIN); also elsewhere on the board

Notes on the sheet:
MCU & COMMS

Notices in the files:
parts and their libraries:
GlacTracker: COPYRIGHT: Copyright (C) 2022 Ultra Librarian. All rights reserved.
SparkFun-Boards: Licensing: Creative Commons ShareAlike 4.0 International - https://creativecommons.org/licenses/by-sa/4.0
Eagle_WE-HCI: Copyright: Würth Elektronik
